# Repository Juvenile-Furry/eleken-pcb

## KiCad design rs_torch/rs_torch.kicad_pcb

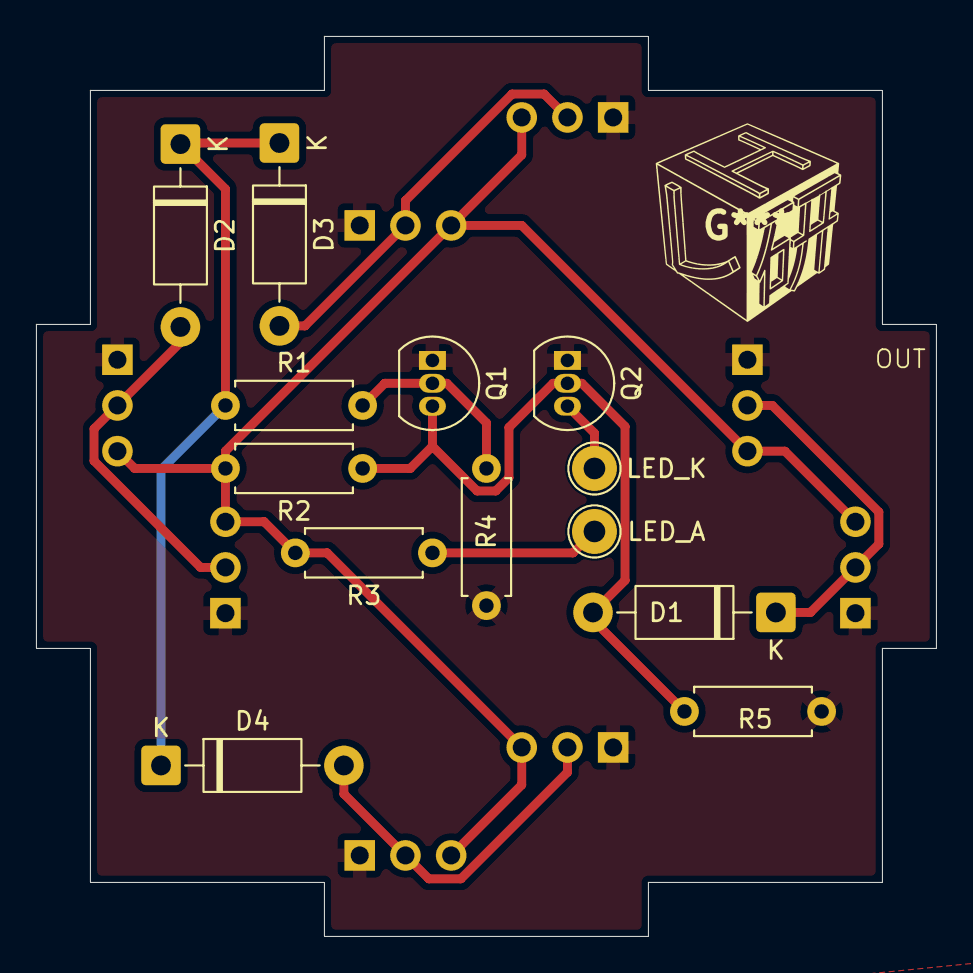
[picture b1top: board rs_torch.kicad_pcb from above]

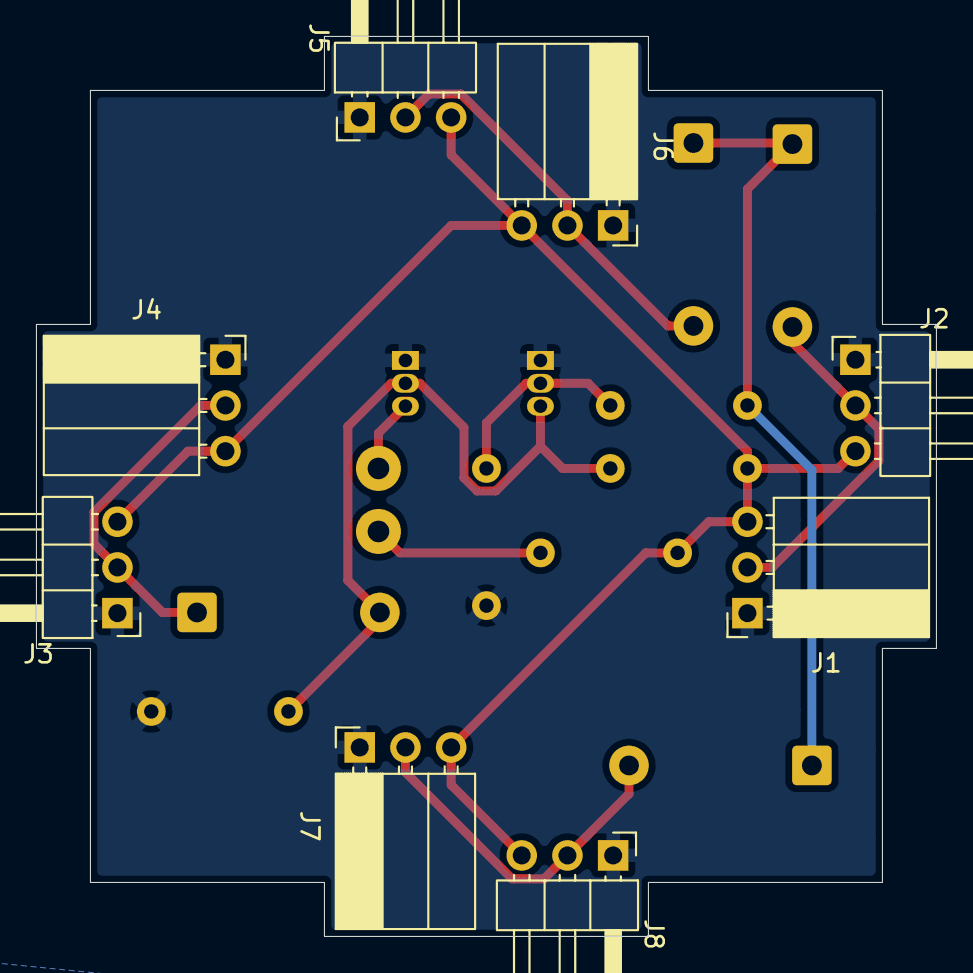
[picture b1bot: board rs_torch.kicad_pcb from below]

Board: 2 copper layers, 50.0 x 50.0 mm, 21 parts (8 on the bottom side), 11 nets.

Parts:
D1, D2, D3, D4: 11EQS06; D_DO-41_SOD81_P10.16mm_Horizontal
J1: INPUT_SOC; PinSocket_1x03_P2.54mm_Horizontal
J2: INPUT_PIN; PinHeader_1x03_P2.54mm_Horizontal
J3: OUTPUT_PIN; PinHeader_1x03_P2.54mm_Horizontal
J4: OUTPUT_SOC; PinSocket_1x03_P2.54mm_Horizontal
J5: INPUT2_PIN; PinHeader_1x03_P2.54mm_Horizontal
J6: INPUT2_SOC; PinSocket_1x03_P2.54mm_Horizontal
J7: INPUT3_SOC; PinSocket_1x03_P2.54mm_Horizontal
J8: INPUT3_PIN; PinHeader_1x03_P2.54mm_Horizontal
Q1, Q2: 2N7000; TO-92_Inline
R1, R2, R3: 10k; R_Axial_DIN0207_L6.3mm_D2.5mm_P7.62mm_Horizontal
R4, R5: 100k; R_Axial_DIN0207_L6.3mm_D2.5mm_P7.62mm_Horizontal
TP1: LED_A; TestPoint_THTPad_D2.5mm_Drill1.2mm
TP2: LED_K; TestPoint_THTPad_D2.5mm_Drill1.2mm

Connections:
+5V: J1.3, J2.3, J3.3, J4.3, J5.3, J6.3, J7.3, J8.3, R2.2, R3.2
/IN: D2.1 (K), D3.1 (K), D4.1 (K), R1.1
/LED_A: R3.1, TP1.1 (1_1)
/LED_K: Q2.3 (D), TP2.1 (1_1)
/OUT: D1.1 (K), J3.2, J4.2
GND: J1.1, J2.1, J3.1, J4.1, J5.1, J6.1, J7.1, J8.1, Q1.1 (S), Q2.1 (S), R4.2, R5.2
unnamed: D1.2 (A), Q1.3 (D), Q2.2 (G), R2.1, R5.1
unnamed: D2.2 (A), J1.2, J2.2
unnamed: D3.2 (A), J5.2, J6.2
unnamed: D4.2 (A), J7.2, J8.2
unnamed: Q1.2 (G), R1.2, R4.1

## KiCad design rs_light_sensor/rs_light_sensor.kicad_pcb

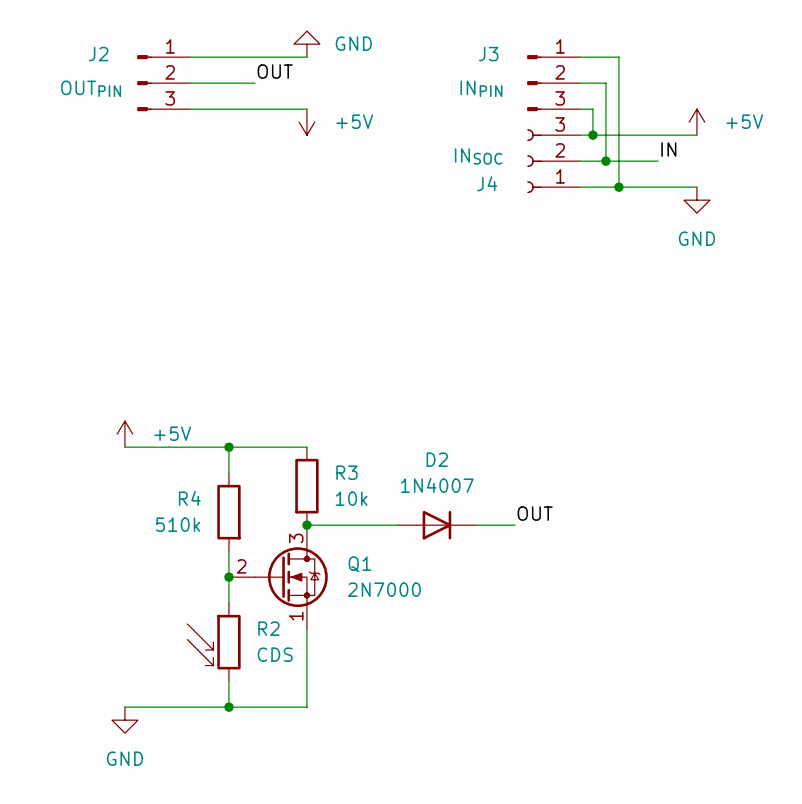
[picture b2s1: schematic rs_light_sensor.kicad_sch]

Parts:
D2: 1N4007; D_DO-35_SOD27_P7.62mm_Horizontal
J2: OUT_{PIN}; PinHeader_1x03_P2.54mm_Vertical
J3: IN_{PIN}; PinHeader_1x03_P2.54mm_Horizontal
J4: IN_{SOC}; PinSocket_1x03_P2.54mm_Horizontal
Q1: 2N7000; TO-92_Inline
R2: CDS; R_LDR_D6.4mm_P3.4mm_Vertical
R3: 10k; R_Axial_DIN0207_L6.3mm_D2.5mm_P7.62mm_Horizontal
R4: 510k; R_Axial_DIN0207_L6.3mm_D2.5mm_P7.62mm_Horizontal

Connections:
+5V: J2.3, J3.3, J4.3, R3.1, R4.1
/IN: J3.2, J4.2
/OUT: D2.1 (K), J2.2
GND: J2.1, J3.1, J4.1, Q1.1 (S), R2.2
unnamed: D2.2 (A), Q1.3 (D), R3.2
unnamed: Q1.2 (G), R2.1, R4.2

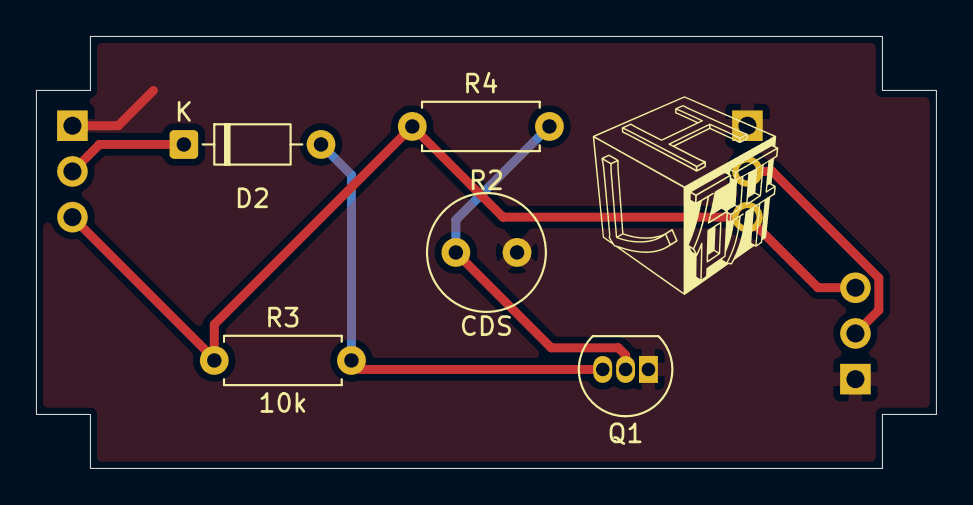
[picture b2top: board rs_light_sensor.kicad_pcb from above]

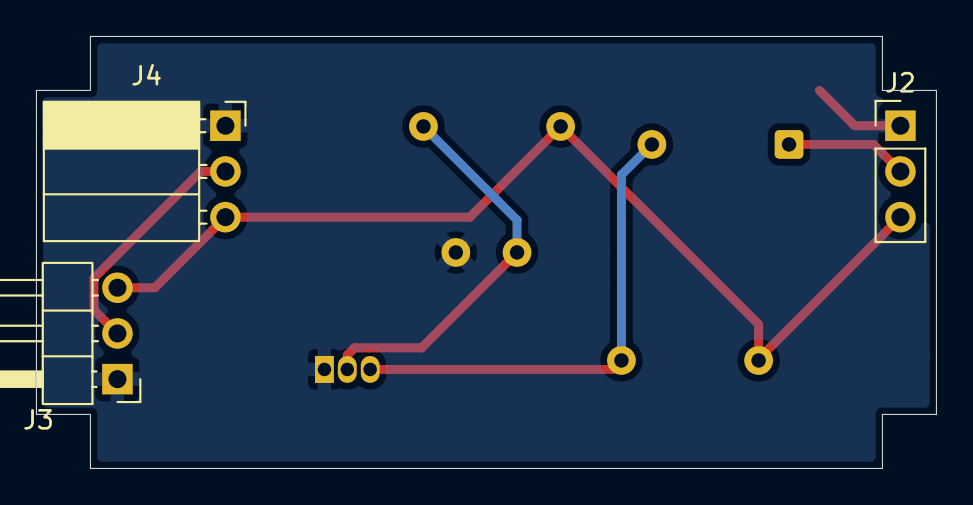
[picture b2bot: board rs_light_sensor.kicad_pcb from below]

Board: 2 copper layers, 50.0 x 24.0 mm, 8 parts (3 on the bottom side), 6 nets.

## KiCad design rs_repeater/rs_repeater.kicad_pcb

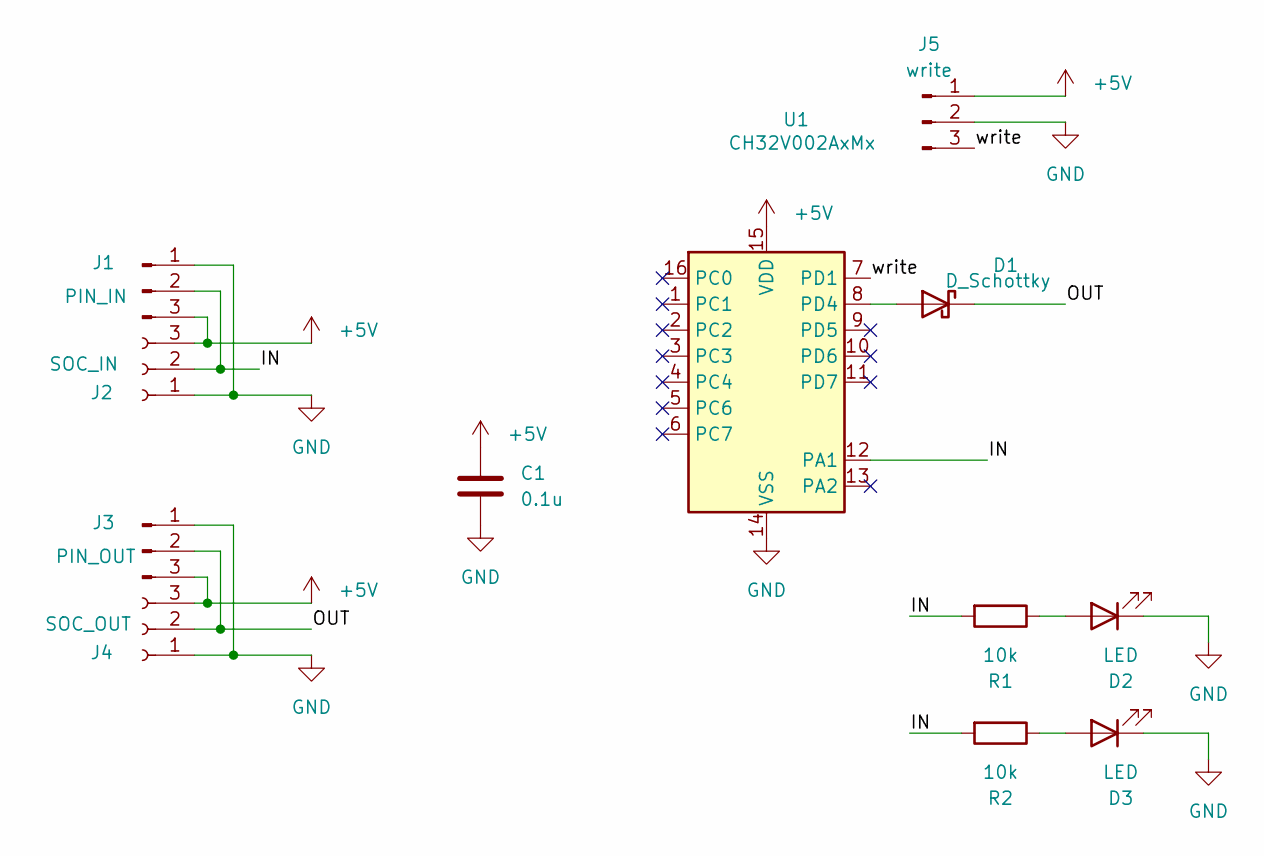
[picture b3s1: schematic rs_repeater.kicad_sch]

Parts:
C1: 0.1u; C_Disc_D10.5mm_W5.0mm_P5.00mm
D1: D_Schottky; D_DO-41_SOD81_P7.62mm_Horizontal
D2, D3: LED; LED_D3.0mm
J1: PIN_IN; PinHeader_1x03_P2.54mm_Horizontal
J2: SOC_IN; PinSocket_1x03_P2.54mm_Horizontal
J3: PIN_OUT; PinHeader_1x03_P2.54mm_Horizontal
J4: SOC_OUT; PinSocket_1x03_P2.54mm_Horizontal
J5: write; PinHeader_1x03_P2.54mm_Vertical
R1, R2: 10k; R_Axial_DIN0207_L6.3mm_D2.5mm_P7.62mm_Horizontal
U1: CH32V002AxMx; STC_SOP-16_3.9x9.9mm_P1.27mm

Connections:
+5V: C1.1, J1.3, J2.3, J3.3, J4.3, J5.1, U1.15 (VDD)
/IN: J1.2, J2.2, R1.2, R2.2, U1.12 (PA1)
/OUT: D1.1 (K), J3.2, J4.2
/write: J5.3, U1.7 (PD1)
GND: C1.2, D2.1 (K), D3.1 (K), J1.1, J2.1, J3.1, J4.1, J5.2, U1.14 (VSS)
unnamed: D1.2 (A), U1.8 (PD4)
unnamed: D2.2 (A), R1.1
unnamed: D3.2 (A), R2.1

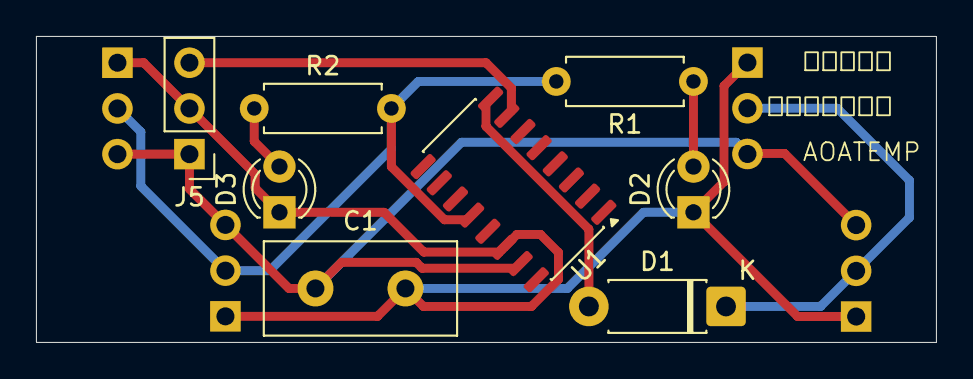
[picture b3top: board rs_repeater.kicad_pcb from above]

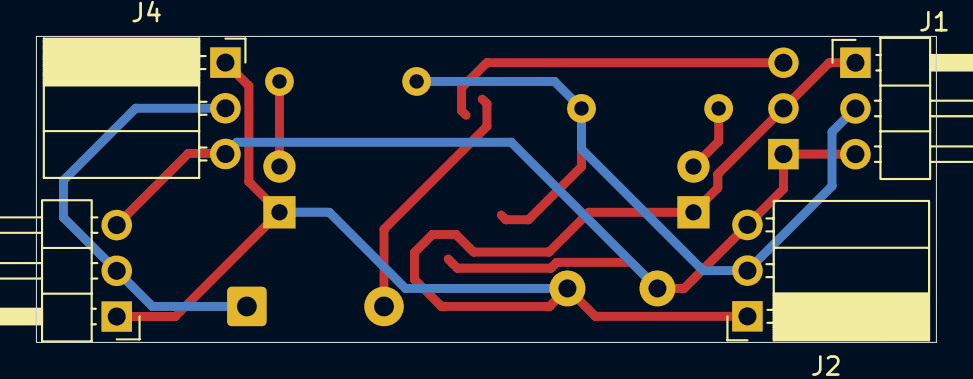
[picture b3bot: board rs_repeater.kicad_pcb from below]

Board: 2 copper layers, 50.0 x 17.0 mm, 12 parts (4 on the bottom side), 8 nets.

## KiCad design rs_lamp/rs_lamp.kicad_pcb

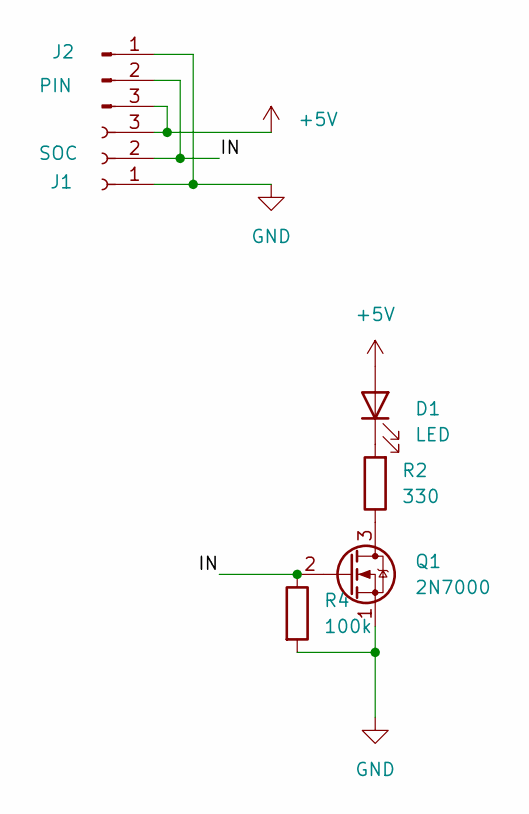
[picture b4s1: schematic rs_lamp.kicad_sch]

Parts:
D1: LED; LED_D3.0mm
J1: SOC; PinSocket_1x03_P2.54mm_Horizontal
J2: PIN; PinHeader_1x03_P2.54mm_Horizontal
Q1: 2N7000; TO-92_Inline
R2: 330; R_Axial_DIN0207_L6.3mm_D2.5mm_P7.62mm_Horizontal
R4: 100k; R_Axial_DIN0207_L6.3mm_D2.5mm_P7.62mm_Horizontal

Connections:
+5V: D1.2 (A), J1.3, J2.3
/IN: J1.2, J2.2, Q1.2 (G), R4.1
GND: J1.1, J2.1, Q1.1 (S), R4.2
unnamed: D1.1 (K), R2.2
unnamed: Q1.3 (D), R2.1

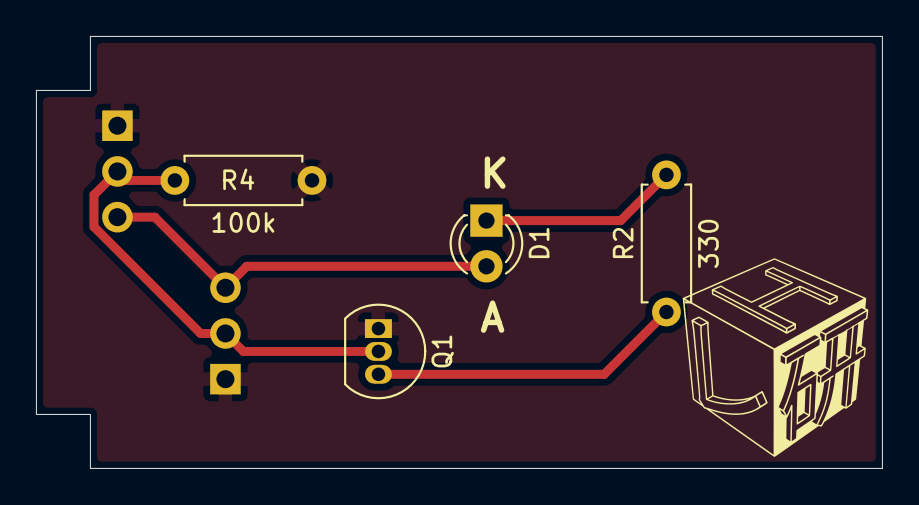
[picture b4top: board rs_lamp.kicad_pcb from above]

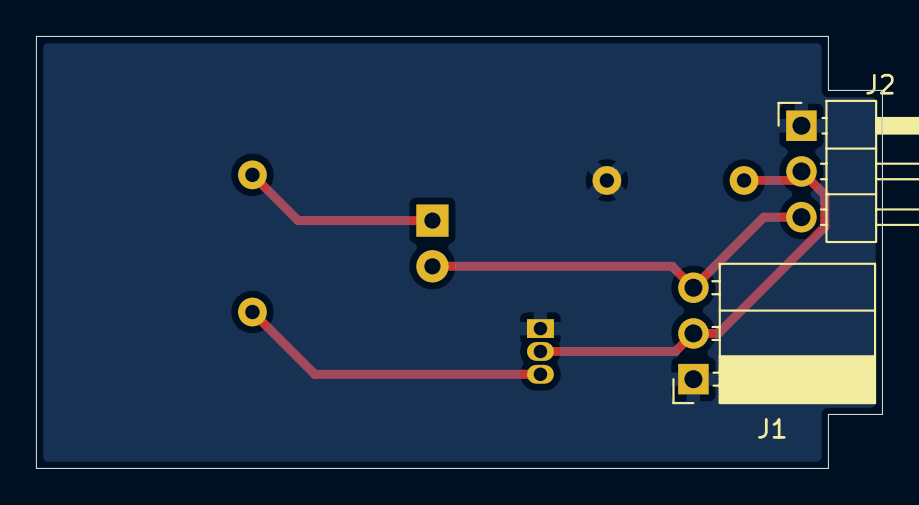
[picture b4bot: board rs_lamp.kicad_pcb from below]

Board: 2 copper layers, 47.0 x 24.0 mm, 6 parts (2 on the bottom side), 5 nets.

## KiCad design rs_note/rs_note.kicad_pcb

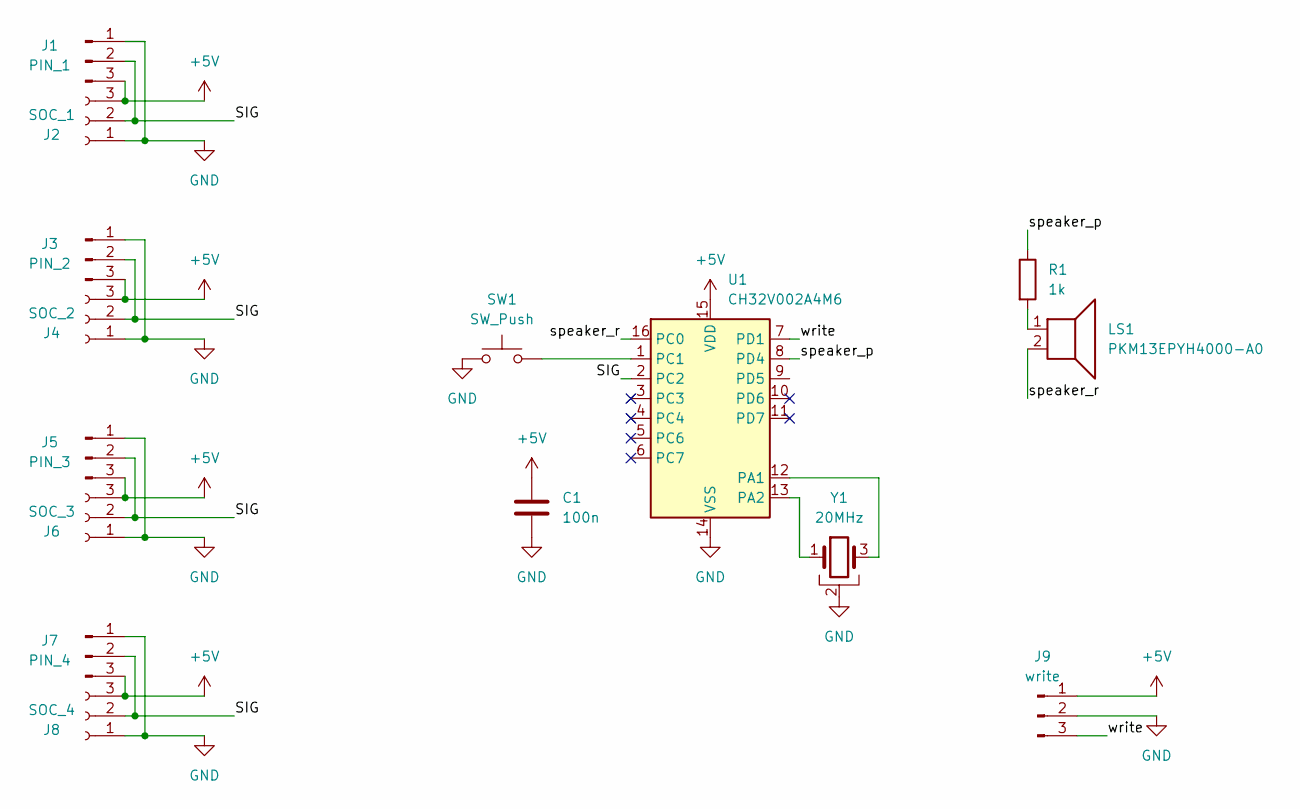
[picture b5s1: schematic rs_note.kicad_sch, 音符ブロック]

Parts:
C1: 100n; C_Disc_D10.5mm_W5.0mm_P5.00mm
J1: PIN_1; PinHeader_1x03_P2.54mm_Horizontal
J2: SOC_1; PinSocket_1x03_P2.54mm_Horizontal
J3: PIN_2; PinHeader_1x03_P2.54mm_Horizontal
J4: SOC_2; PinSocket_1x03_P2.54mm_Horizontal
J5: PIN_3; PinHeader_1x03_P2.54mm_Horizontal
J6: SOC_3; PinSocket_1x03_P2.54mm_Horizontal
J7: PIN_4; PinHeader_1x03_P2.54mm_Horizontal
J8: SOC_4; PinSocket_1x03_P2.54mm_Horizontal
J9: write; PinHeader_1x03_P2.54mm_Vertical
LS1: PKM13EPYH4000-A0; Buzzer_TDK_PS1240P02BT_D12.2mm_H6.5mm
R1: 1k; R_Axial_DIN0207_L6.3mm_D2.5mm_P7.62mm_Horizontal
SW1: SW_Push; SW_PUSH_6mm
U1: CH32V002A4M6; STC_SOP-16_3.9x9.9mm_P1.27mm
Y1: 20MHz; Resonator_Murata_CSTLSxxxX-3Pin_W5.5mm_H3.0mm

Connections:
+5V: C1.1, J1.3, J2.3, J3.3, J4.3, J5.3, J6.3, J7.3, J8.3, J9.1, U1.15 (VDD)
/SIG: J1.2, J2.2, J3.2, J4.2, J5.2, J6.2, J7.2, J8.2, U1.2 (PC2)
/speaker_p: R1.1, U1.8 (PD4)
/speaker_r: LS1.2, U1.16 (PC0)
/write: J9.3, U1.7 (PD1)
GND: C1.2, J1.1, J2.1, J3.1, J4.1, J5.1, J6.1, J7.1, J8.1, J9.2, SW1.2, U1.14 (VSS), Y1.2
unnamed: LS1.1, R1.2
unnamed: U1.12 (PA1), Y1.3
unnamed: U1.13 (PA2), Y1.1
unnamed: SW1.1, U1.1 (PC1)

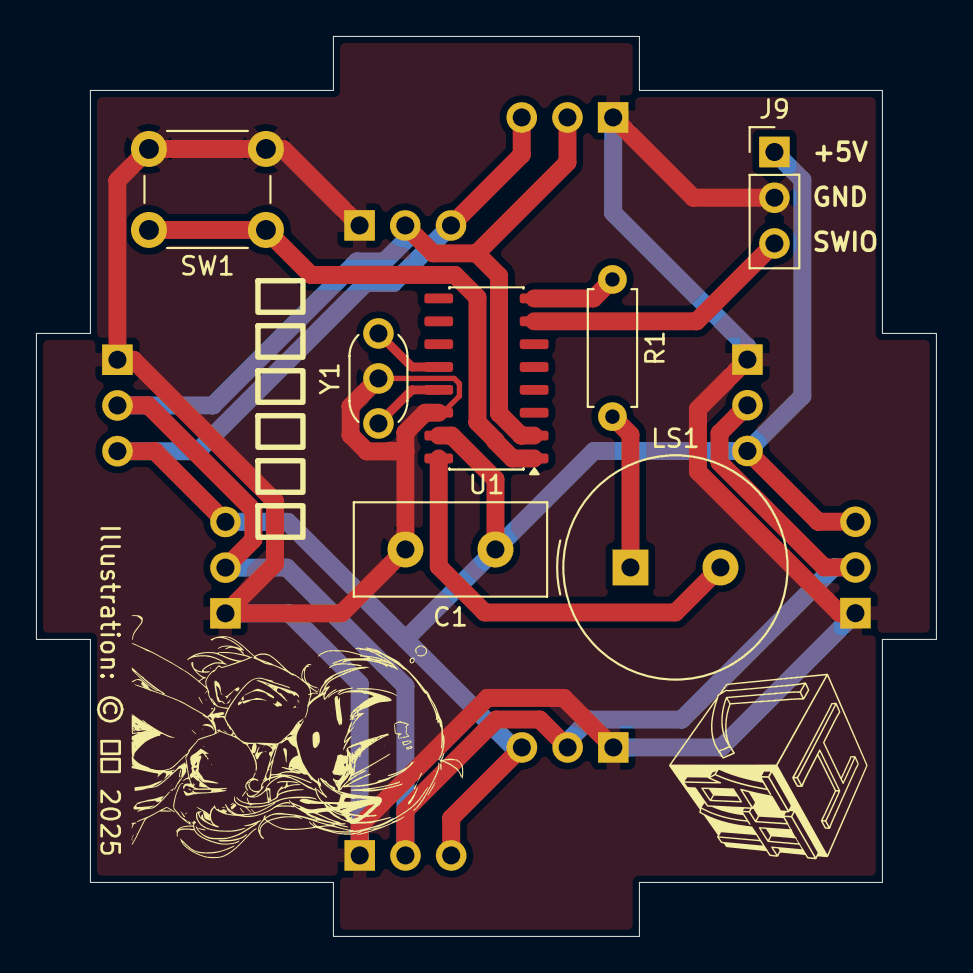
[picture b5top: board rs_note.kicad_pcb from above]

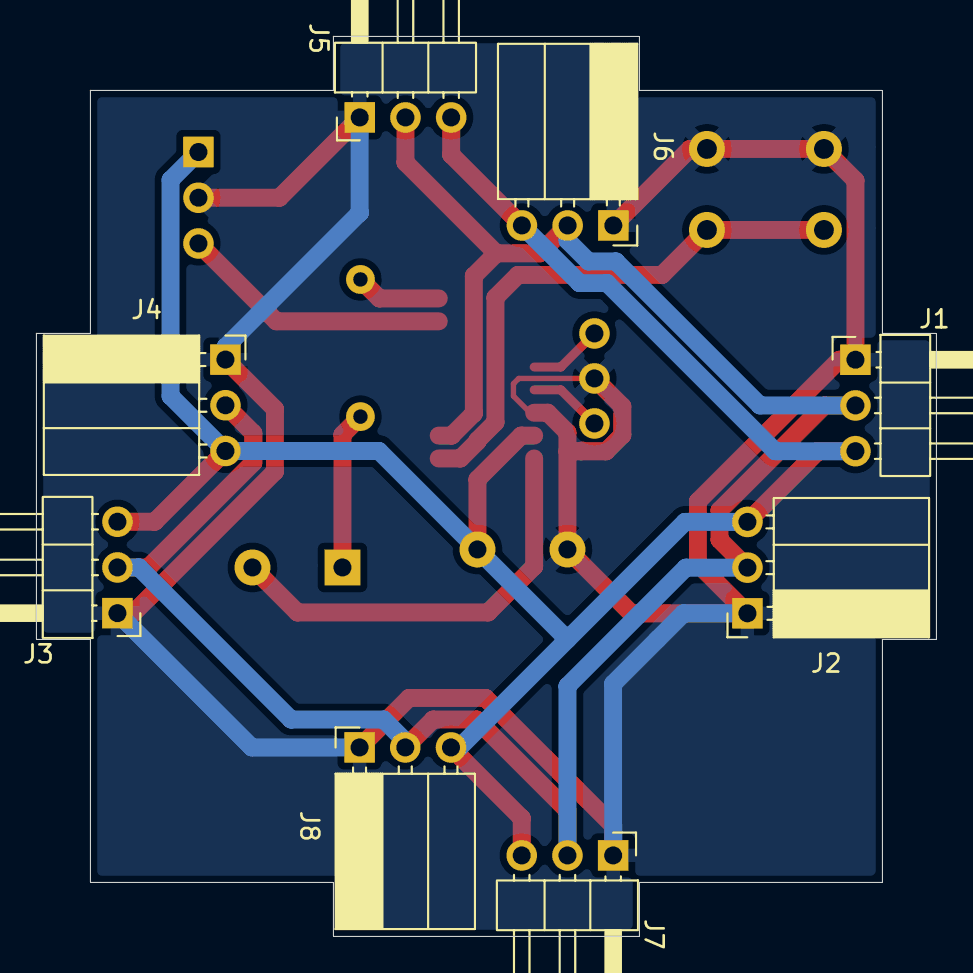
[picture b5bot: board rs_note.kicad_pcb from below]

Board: 2 copper layers, 50.0 x 50.0 mm, 15 parts (8 on the bottom side), 10 nets.

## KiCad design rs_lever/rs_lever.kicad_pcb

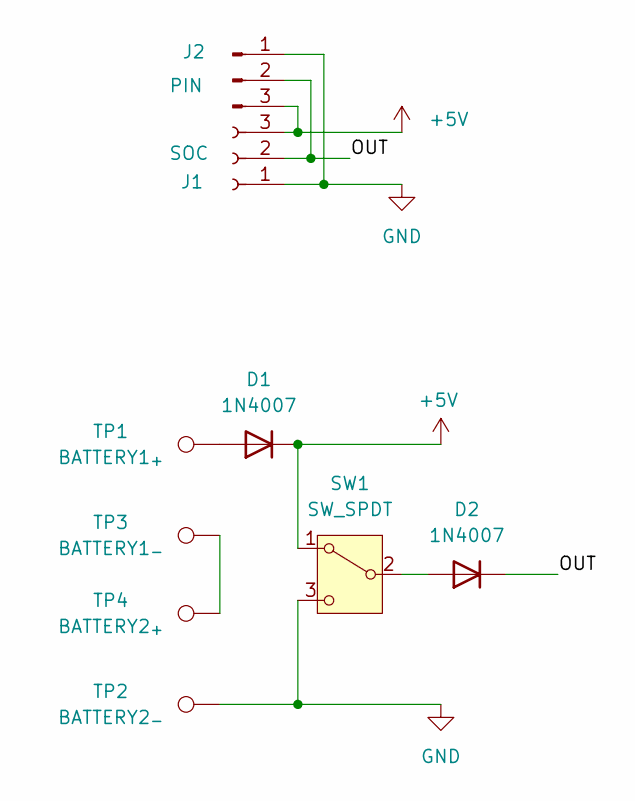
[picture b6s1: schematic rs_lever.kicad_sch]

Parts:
D1, D2: 1N4007; D_DO-35_SOD27_P7.62mm_Horizontal
J1: SOC; PinSocket_1x03_P2.54mm_Horizontal
J2: PIN; PinHeader_1x03_P2.54mm_Horizontal
SW1: SW_SPDT; SW_Lever_1P2T_NKK_GW12LxH
TP1: BATTERY1_{+}; TestPoint_THTPad_D2.5mm_Drill1.2mm
TP2: BATTERY2_{-}; TestPoint_THTPad_D2.5mm_Drill1.2mm
TP3: BATTERY1_{-}; TestPoint_THTPad_D2.5mm_Drill1.2mm
TP4: BATTERY2_{+}; TestPoint_THTPad_D2.5mm_Drill1.2mm

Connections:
+5V: D1.1 (K), J1.3, J2.3, SW1.1 (A)
/OUT: D2.1 (K), J1.2, J2.2
GND: J1.1, J2.1, SW1.3 (C), TP2.1 (1_1)
unnamed: D1.2 (A), TP1.1 (1_1)
unnamed: D2.2 (A), SW1.2 (B)
unnamed: TP3.1 (1_1), TP4.1 (1_1)

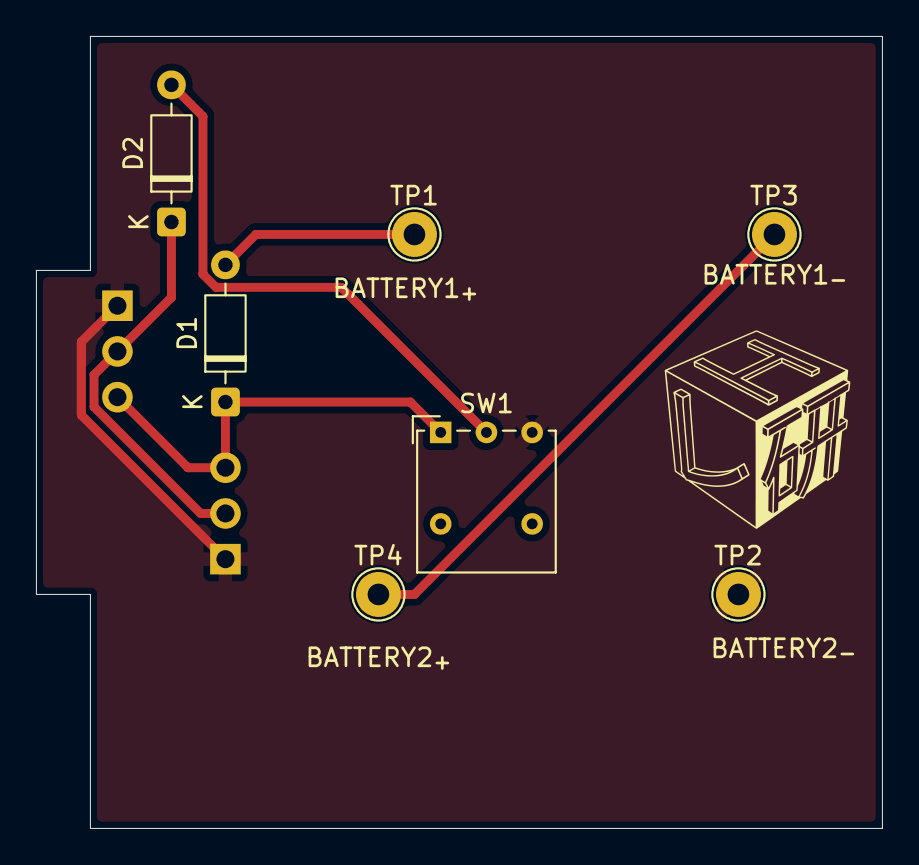
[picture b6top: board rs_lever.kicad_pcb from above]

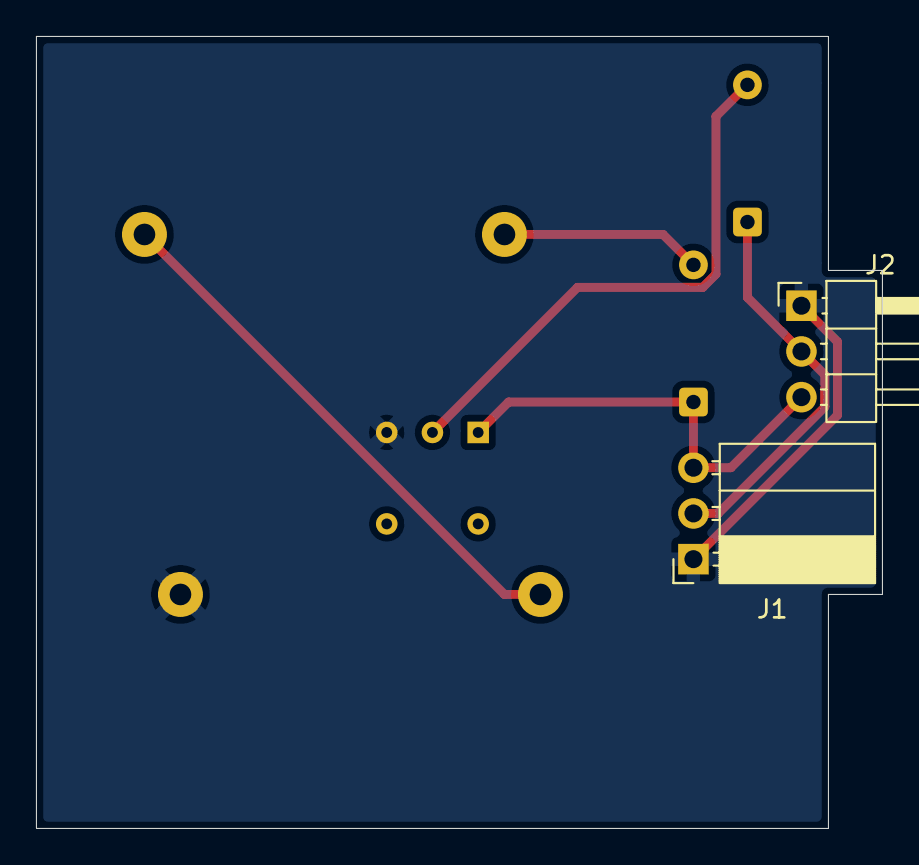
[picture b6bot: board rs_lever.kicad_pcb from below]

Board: 2 copper layers, 47.0 x 44.0 mm, 9 parts (2 on the bottom side), 6 nets.

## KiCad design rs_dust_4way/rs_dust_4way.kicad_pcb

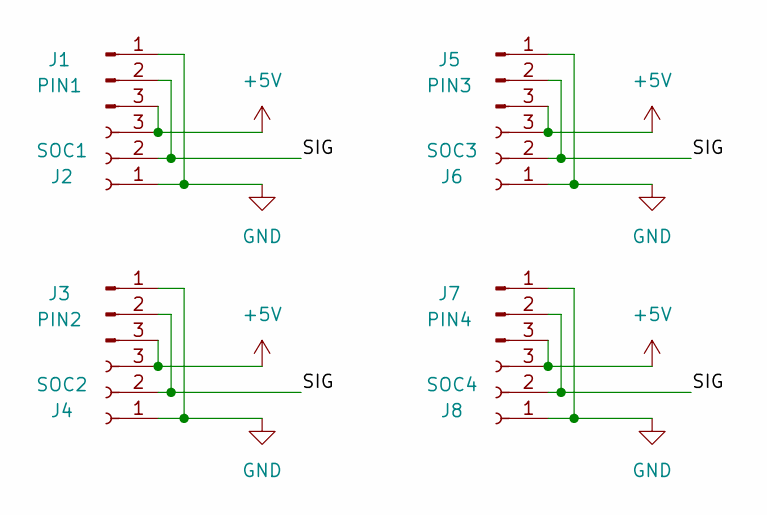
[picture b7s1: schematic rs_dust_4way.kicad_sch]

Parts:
J1: PIN1; PinHeader_1x03_P2.54mm_Horizontal
J2: SOC1; PinSocket_1x03_P2.54mm_Horizontal
J3: PIN2; PinHeader_1x03_P2.54mm_Horizontal
J4: SOC2; PinSocket_1x03_P2.54mm_Horizontal
J5: PIN3; PinHeader_1x03_P2.54mm_Horizontal
J6: SOC3; PinSocket_1x03_P2.54mm_Horizontal
J7: PIN4; PinHeader_1x03_P2.54mm_Horizontal
J8: SOC4; PinSocket_1x03_P2.54mm_Horizontal

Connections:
+5V: J1.3, J2.3, J3.3, J4.3, J5.3, J6.3, J7.3, J8.3
/SIG: J1.2, J2.2, J3.2, J4.2, J5.2, J6.2, J7.2, J8.2
GND: J1.1, J2.1, J3.1, J4.1, J5.1, J6.1, J7.1, J8.1

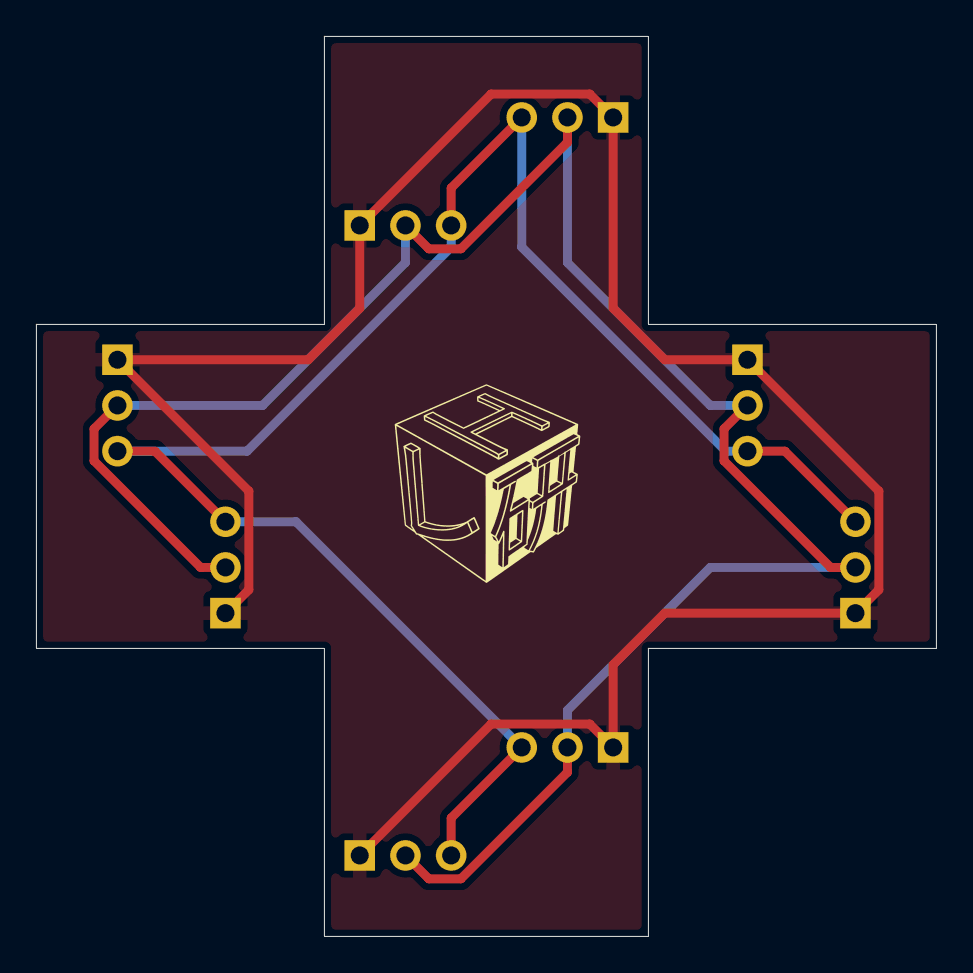
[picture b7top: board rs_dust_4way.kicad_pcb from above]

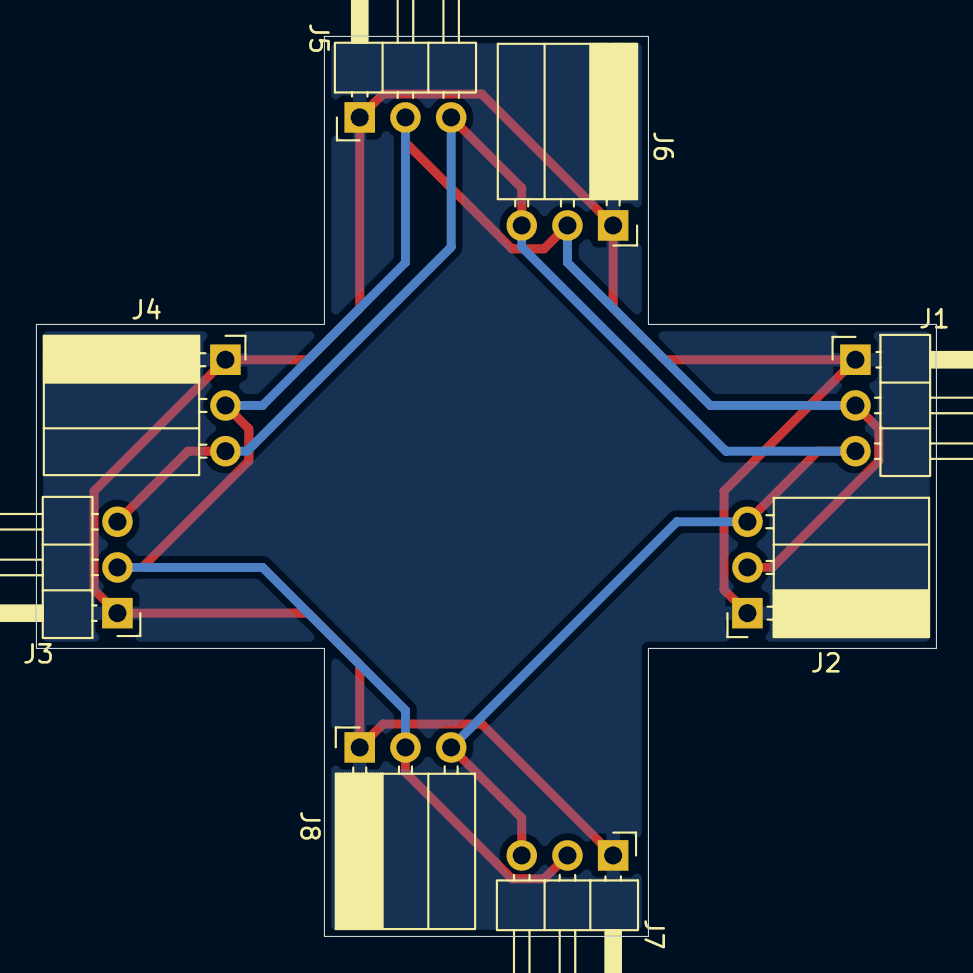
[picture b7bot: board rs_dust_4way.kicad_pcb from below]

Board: 2 copper layers, 50.0 x 50.0 mm, 8 parts (8 on the bottom side), 3 nets.
